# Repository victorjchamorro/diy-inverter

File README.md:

# diy-inverter
Creación de un inversor partiendo de un Xantrex ProWatt 1400i averiado

Serie de vídeos en youtube:
[youtube](https://www.youtube.com/playlist?list=PLBt3mBwJQwRWf2Qoqq8KDot9ghxqB0hle)

Imágenes:

La idea es remplazar toda la electrónica de control por un circuito nuevo, aprovechando los componentes de potencia existentes en la placa

- arduino: arduino code
- kicad: schemas and gerbers
- pictures: fotografías
- utl: utilidades

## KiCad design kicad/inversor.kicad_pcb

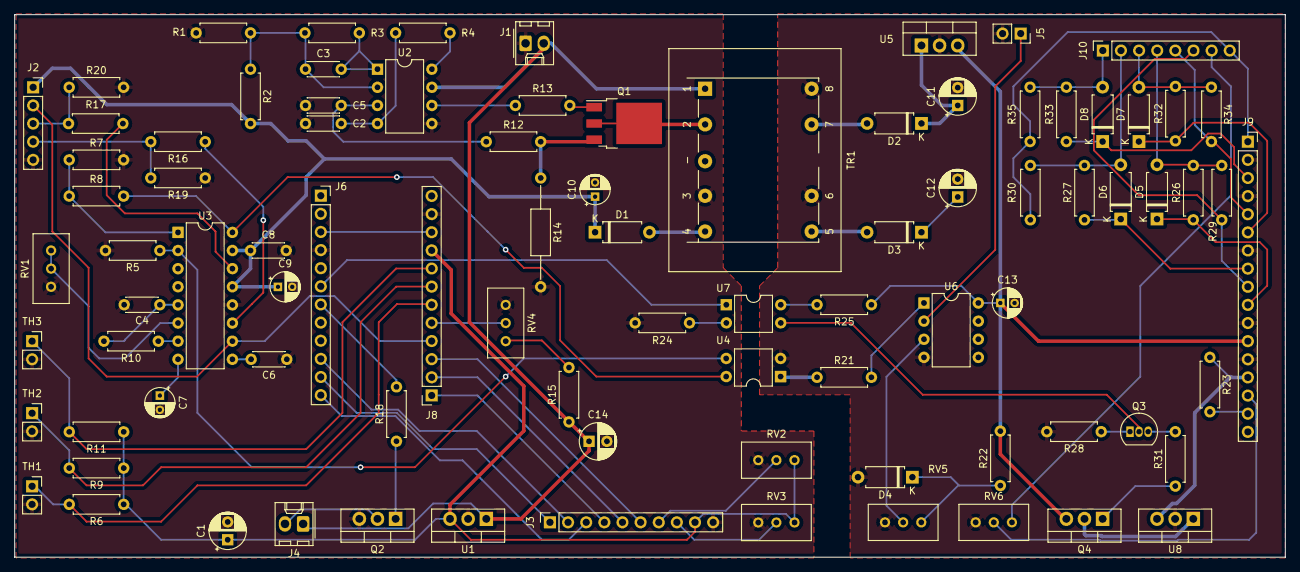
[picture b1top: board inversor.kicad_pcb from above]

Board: 2 copper layers, 178.0 x 76.0 mm, 88 parts (0 on the bottom side), 78 nets.

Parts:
C1, C14: 250nF; CP_Radial_D5.0mm_P2.50mm
C2: 1nF; C_Disc_D4.3mm_W1.9mm_P5.00mm
C3: 100pF; C_Disc_D4.3mm_W1.9mm_P5.00mm
C4: 10nF; C_Disc_D4.3mm_W1.9mm_P5.00mm
C5: 330pF; C_Disc_D4.3mm_W1.9mm_P5.00mm
C6, C8: 100nF; C_Disc_D4.3mm_W1.9mm_P5.00mm
C7: 1uF; CP_Radial_D4.0mm_P2.00mm
C9, C10, C13: 470uF; CP_Radial_D4.0mm_P2.00mm
C11, C12: 10uF; CP_Radial_D5.0mm_P2.50mm
D1, D2, D3: D; D_A-405_P7.62mm_Horizontal
D4: 4.7v; D_A-405_P7.62mm_Horizontal
D5, D6, D7, D8: IN4148; D_A-405_P7.62mm_Horizontal
J1: VCC; Molex_KK-254_AE-6410-02A_1x02_P2.54mm_Vertical
J2: PWM; PinSocket_1x05_P2.54mm_Vertical
J3: LCD 16x2; PinSocket_1x10_P2.54mm_Vertical
J4: MainFan; Molex_KK-254_AE-6410-02A_1x02_P2.54mm_Vertical
J5: 380VFreed; PinSocket_1x02_P2.54mm_Vertical
J6: PRO_MINI_L; PinSocket_1x12_P2.54mm_Vertical
J8: PRO_MINI_R; PinSocket_1x12_P2.54mm_Vertical
J9: SPWM Driver Board; PinSocket_1x17_P2.54mm_Vertical
J10: To IGBTs; PinSocket_1x08_P2.54mm_Vertical
Q1: SSF6014D; TO-252-3_TabPin2
Q2: TIP120; TO-220-3_Vertical
Q3: S8050; TO-92_Inline
Q4: TIP125; TO-220-3_Vertical
R1, R15: 2K2; R_Axial_DIN0207_L6.3mm_D2.5mm_P7.62mm_Horizontal
R2: 12K4; R_Axial_DIN0207_L6.3mm_D2.5mm_P7.62mm_Horizontal
R3: 100K; R_Axial_DIN0207_L6.3mm_D2.5mm_P7.62mm_Horizontal
R4: 9K3; R_Axial_DIN0207_L6.3mm_D2.5mm_P7.62mm_Horizontal
R5, R6, R7, R8, R9, R11, R18, R19, R20, R21, R22, R23, R24, R25, R28, R29, R30, R34, R35: 10K; R_Axial_DIN0207_L6.3mm_D2.5mm_P7.62mm_Horizontal
R10: 47R; R_Axial_DIN0207_L6.3mm_D2.5mm_P7.62mm_Horizontal
R12: 1K; R_Axial_DIN0207_L6.3mm_D2.5mm_P7.62mm_Horizontal
R13: 4R7; R_Axial_DIN0207_L6.3mm_D2.5mm_P7.62mm_Horizontal
R14: 0.05; R_Axial_DIN0207_L6.3mm_D2.5mm_P15.24mm_Horizontal
R16, R17: 10R; R_Axial_DIN0207_L6.3mm_D2.5mm_P7.62mm_Horizontal
R26, R27, R32, R33: 4.7R; R_Axial_DIN0207_L6.3mm_D2.5mm_P7.62mm_Horizontal
R31: 800R; R_Axial_DIN0207_L6.3mm_D2.5mm_P7.62mm_Horizontal
RV1, RV2, RV3, RV4, RV5, RV6: 10K; Potentiometer_Bourns_3296W_Vertical
TH1: NTC1; PinSocket_1x02_P2.54mm_Vertical
TH2: NTC2; PinSocket_1x02_P2.54mm_Vertical
TH3: NTC3; PinSocket_1x02_P2.54mm_Vertical
TR1: TRFLYBACK; Transformer_BlyBack_custom_01
U1: L7805; TO-220-3_Vertical
U2: UC3845; DIP-8_W7.62mm
U3: SG3525; DIP-16_W7.62mm
U4, U7: EL817; DIP-4_W7.62mm
U5: L7812; TO-220-3_Vertical
U6: LM358; DIP-8_W7.62mm
U8: LM7805_TO220; TO-220-3_Vertical

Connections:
1HO: D7.2 (A), J10.3, R32.2, R34.1
1LO: D8.2 (A), J10.1, R33.2, R35.1
2HO: D5.2 (A), J10.4, R26.2, R29.1
2LO: D6.2 (A), J10.2, R27.2, R30.1
+5V: C1.1, J3.9, J8.9, R6.1, R9.1, R11.1, RV2.1, RV3.1, U1.3 (OUT)
+12V: C13.1, J9.12, Q4.3 (E), R22.2, R25.1, U5.3 (OUT), U6.8 (V+)
+15V: C8.1, C9.1, C10.1, D1.1 (K), J2.1, R2.2, U3.13 (VC), U3.15 (VIN)
/SPWM/5v: J9.14, R23.1, U8.3 (VO)
A0: J8.5, RV4.2
A1: J8.6, R6.2, TH1.1
A2: J8.7, R9.2, TH2.1
A3: J8.8, R11.2, TH3.1
D3: J6.6, U7.1
D4: J6.7, R18.2
D7: J3.2, J6.10
D8: J3.1, J6.11
D9: J3.3, J6.12
D10: J3.4, J8.1
D11: J3.5, J8.2
D12: J3.6, J8.3
D13: J2.2, J8.4, U3.10 (SD)
GND: C1.2, C2.2, C4.2, C5.2, C6.1, C7.2, C8.2, C9.2, C10.2, C14.2, J1.1, J2.5, J3.10, J6.4, J8.11, Q2.3 (E), R1.1, R5.2, R7.2, R14.2, R19.1, R20.2, R24.2, RV1.3, RV2.3, RV3.3, RV4.3, TH1.2, TH2.2, TH3.2, TR1.3, U1.2 (GND), U2.5 (GND), U3.12 (GND)
GND2: C11.2, C12.2, C13.2, D4.2 (A), J5.2, J9.2, J9.4, J9.7, J9.11, J9.13, R28.2, RV5.3, RV6.3, TR1.6, TR1.8, U4.2, U5.2 (GND), U6.4 (V-), U8.2 (GND)
IFB: J9.1, J10.8, R30.2, R35.2
NI: R5.1, U3.2 (NI), U4.3
unnamed: C2.1, R4.1, U2.4 (RC)
unnamed: C3.1, R1.2, R2.1, R3.1, U2.2 (FB)
unnamed: C3.2, R3.2, U2.1 (COMP)
unnamed: C4.1, R10.2, U3.5 (CT)
unnamed: C5.1, R12.1, U2.3 (CS)
unnamed: C6.2, U3.9 (COMP)
unnamed: C7.1, U3.8 (SS)
unnamed: C11.1, D2.1 (K), U5.1 (IN)
unnamed: C12.1, D3.1 (K)
unnamed: D1.2 (A), TR1.4
unnamed: D2.2 (A), TR1.7
unnamed: D3.2 (A), TR1.5
unnamed: D4.1 (K), R22.1, RV5.1
unnamed: D5.1 (K), J9.10, R26.1
unnamed: D6.1 (K), J9.8, R27.1
unnamed: D7.1 (K), J9.6, R32.1
unnamed: D8.1 (K), J9.3, R33.1
unnamed: J3.7, RV2.2
unnamed: J3.8, RV3.2
unnamed: J4.2, Q2.2 (C)
unnamed: J5.1, U6.2 (-)
unnamed: J9.15, RV6.2
unnamed: J9.16, R23.2
unnamed: J10.7, RV6.1
unnamed: Q1.1 (G), R13.2
unnamed: Q1.2 (D), TR1.2
unnamed: Q1.3 (S), R12.2, R14.1
unnamed: Q2.1 (B), R18.1
unnamed: Q3.1 (E), R28.1
unnamed: Q3.2 (B), U7.3
unnamed: Q3.3 (C), R31.2
unnamed: Q4.1 (B), R31.1
unnamed: Q4.2 (C), U8.1 (VI)
unnamed: R4.2, U2.8 (VREF)
unnamed: R7.1, R8.1, U3.1 (INV)
unnamed: R10.1, U3.7 (DISCH)
unnamed: R13.1, U2.6 (OUT)
unnamed: R15.2, RV4.1
unnamed: R16.1, U3.11 (OUTA)
unnamed: R17.1, U3.14 (OUTB)
unnamed: R21.1, U4.1
unnamed: R21.2, U6.1
unnamed: R24.1, U7.2
unnamed: R25.2, U7.4
unnamed: RV1.1, RV1.2, U3.6 (RT)
unnamed: RV5.2, U6.3 (+)
PWM_Out_A: J2.4, R16.2, R19.2
PWM_Out_B: J2.3, R17.2, R20.1
REF: R8.2, U3.16 (REF), U4.4
RST: J6.3, J8.10
VCC: C14.1, J1.2, J4.1, R15.1, TR1.1, U1.1 (IN), U2.7 (VCC)
VS1: J9.5, J10.5, R34.2
VS2: J9.9, J10.6, R29.2

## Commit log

2023-08-04 Versión 1.0 mandada a fabricar prototipo
2023-08-04 Mejorado README.md
2023-08-04 FIX: VCC Arduino 5v en lugar de VCC FIX: Divisor de tension para sensor de voltaje de batería con resistencia en la parte de vcc en lugar de gnd
2023-08-04 Esquema en pdf
2023-08-05 Cambio Arduino por el ATMega328
2023-08-13 Fix: - Agregado condensador en la linea VCC - Agregada línea entre D13 del arduino y DS del SG3525 para poder detenerlo - Ajustes en pistas
2023-08-29 Agregadas la mediciones de los 3 sensores de temperatura al LCD y a los chequeos
2023-08-30 Ajustes firmware arduino: mejoras ruido LCD y calibraciones
2023-09-01 Ajustes en temperaturas para el manejo del ventilador
